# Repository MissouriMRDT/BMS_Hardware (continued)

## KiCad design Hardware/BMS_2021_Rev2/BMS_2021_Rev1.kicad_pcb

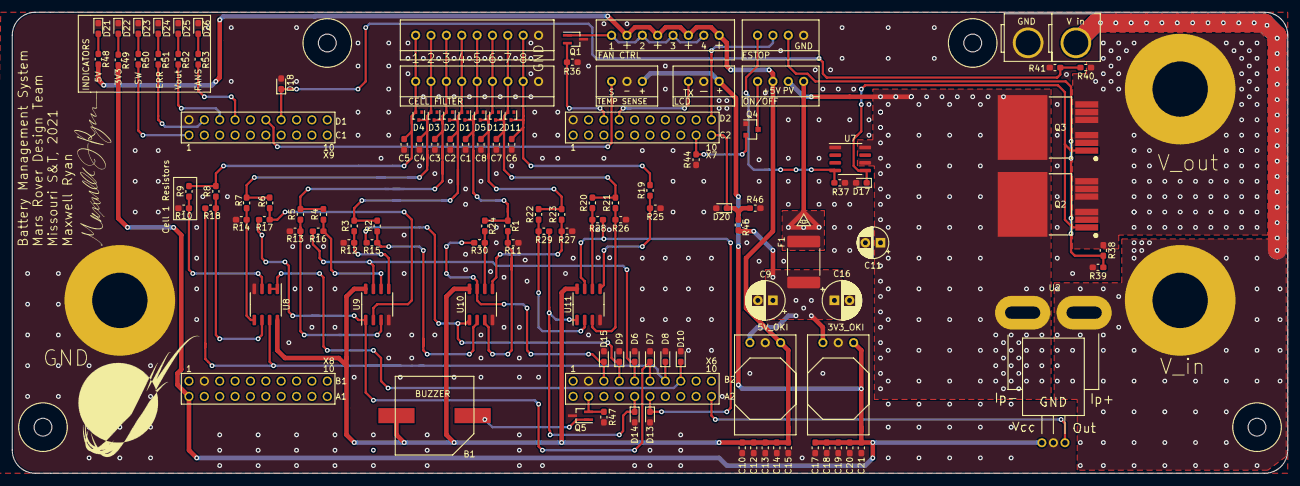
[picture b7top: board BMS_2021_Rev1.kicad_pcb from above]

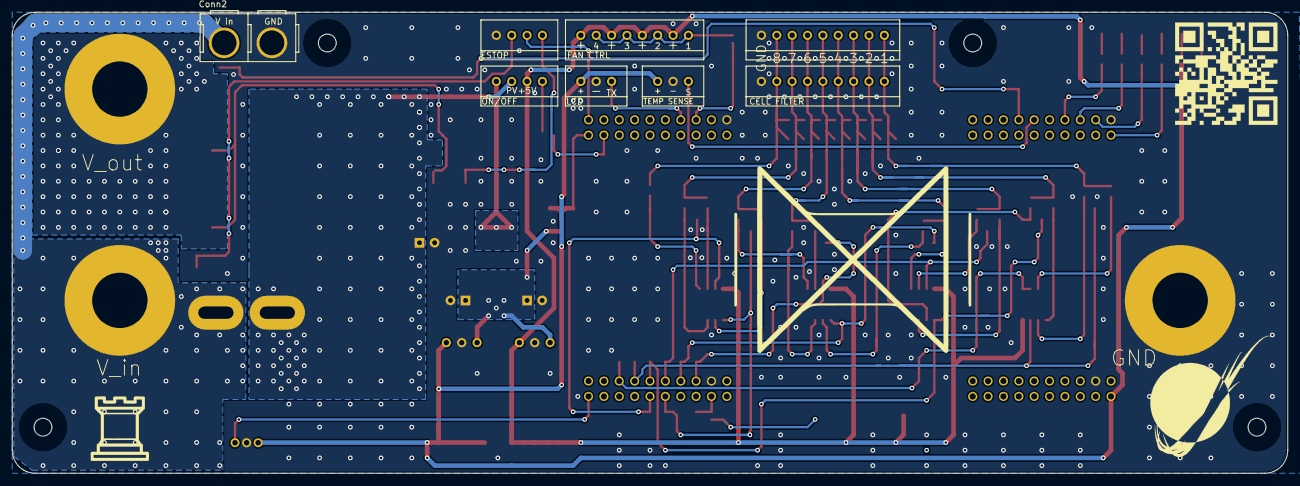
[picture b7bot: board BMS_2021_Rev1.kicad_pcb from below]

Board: 2 copper layers, 210.8 x 76.2 mm, 118 parts (8 on the bottom side), 64 nets.

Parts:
B1: Buzzer; BUZZER_SMI_1324_TW_5V_2_R
C1, C2, C3, C4, C5, C6, C7, C8: 1u; C_0603_1608Metric_Pad1.05x0.95mm_HandSolder
C9, C16: 22u 50V; CP_Radial_D6.3mm_P2.50mm
C10, C12, C13, C14, C17, C18, C19, C20: 10u; C_0603_1608Metric_Pad1.05x0.95mm_HandSolder
C11: 10u; CP_Radial_D5.0mm_P2.50mm
C15, C21: 0.1u; C_0603_1608Metric_Pad1.05x0.95mm_HandSolder
Conn1, Conn6: cell_filter; MOLEX_SL_09_Vertical
Conn2: V_in; Anderson_2_Vertical_Sidy_by_Side
Conn3, Conn7: Molex_SL_03; MOLEX_SL_03_Vertical
Conn4: Molex_SL_08; MOLEX_SL_08_Vertical
Conn5: Molex_SL_04; MOLEX_SL_04_Vertical
D1, D2, D3, D4, D5, D11, D12: 5V_Schottky; SOT-416
D6, D7, D8, D9, D10, D13, D14, D15, D17, D18, D20: 3V3_Zener; D_0603_1608Metric_Pad1.05x0.95mm_HandSolder
D21, D22, D23, D24, D25, D26: LED; LED_0603_1608Metric_Pad1.05x0.95mm_HandSolder
F1: Polyfuse; Fuse_2920_7451Metric
Q1, Q5: 2N7002PW; SOT-323_SC-70_Handsoldering
Q2, Q3: IRFS7530TRL7PP; TO127P1524X483-7N
Q4: 2N7002; SOT-23
R1, R2, R3, R4, R5, R6, R7, R8, R19, R20, R21, R22, R23, R24: 8.2M; R_0603_1608Metric_Pad1.05x0.95mm_HandSolder
R9, R36, R37, R39, R44, R47: 10k; R_0603_1608Metric_Pad1.05x0.95mm_HandSolder
R10: 36.5k; R_0603_1608Metric_Pad1.05x0.95mm_HandSolder
R11, R12, R13, R14, R15, R16, R17, R18, R25, R26, R27, R28, R29, R30: 6.34M; R_0603_1608Metric_Pad1.05x0.95mm_HandSolder
R38: 4k; R_0603_1608Metric_Pad1.05x0.95mm_HandSolder
R40, R45: 3.32M; R_0603_1608Metric_Pad1.05x0.95mm_HandSolder
R41, R46: 360k; R_0603_1608Metric_Pad1.05x0.95mm_HandSolder
R48: 500; R_0603_1608Metric_Pad1.05x0.95mm_HandSolder
R49, R50, R51, R52, R53: 330; R_0603_1608Metric_Pad1.05x0.95mm_HandSolder
SW1: Relay_SPST; MOLEX_SL_04_Vertical
U1: TM4C129E_Launchpad; TM4C129E_Launchpad_FULL_THT_TOP
U2: ACS759ECB-200B-PFF-T; ACS759ECB_PFF_Leadform_5pins
U5: 5V_OKI; OKI_Horizontal
U6: 3V3_OKI; OKI_Horizontal
U7: LT1910; LT1910_SOIC-8-1EP_3.9x4.9mm_P1.27mm_EP2.41x3.3mm
U8, U9, U10, U11: LM358; SO-8_3.9x4.9mm_P1.27mm
V1, V2, V3: BATT_PWR_VIA

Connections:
+3V3: C17.1, C18.1, C19.1, C20.1, C21.1, Conn3.3, Conn7.3, R49.1, U1.+3V3, U2.1, U6.3
+5V: B1.1, C10.1, C12.1, C13.1, C14.1, C15.1, Conn4.2, Conn4.4, Conn4.6, Conn4.8, R48.1, SW1.2, U5.3, U8.8, U9.8, U10.8, U11.8
/ESTOP/V_out: Q2.2, Q2.3, Q2.5, Q2.6, Q2.7, Q3.2, Q3.3, Q3.5, Q3.6, Q3.7, R38.1, R40.1, V3.1
/FANS_IND: R53.1, U1.PH3
/LCD_TX: Conn7.1, U1.PA7
/PV: C11.1, Q2.4, Q3.4, SW1.3, U2.5, U7.6, U7.8
/V_in: Conn2.2, U2.4, V1.1
/V_out_ind: R52.1, U1.PH2
/V_out_sense: D18.1, R40.2, R41.1, U1.PD0
/buzzer_control: Q5.2, R47.1, U1.PD2
/cell_1: C5.2, Conn1.1, Conn6.1, D4.2, R8.2, R9.2
/cell_1_sense: D10.1, U1.PK3, U8.1, U8.2
/cell_2: C4.2, Conn1.2, Conn6.2, D3.2, D4.3, R6.2, R7.2
/cell_2_sense: D8.1, R18.1, U1.PK2, U8.7
/cell_3: C3.2, Conn1.3, Conn6.3, D2.2, D3.3, R4.2, R5.2
/cell_3_sense: D7.1, R17.1, U1.PK1, U9.1
/cell_4: C2.2, Conn1.4, Conn6.4, D1.2, D2.3, R2.2, R3.2
/cell_4_sense: D6.1, R16.1, U1.PK0, U9.7
/cell_5_sense: D9.1, R15.1, U1.PB5, U10.1
/cell_6: C8.2, Conn1.6, Conn6.6, D5.3, D12.2, R22.2, R23.2
/cell_6_sense: D15.1, R30.1, U1.PB4, U10.7
/cell_7: C7.2, Conn1.7, Conn6.7, D11.2, D12.3, R20.2, R21.2
/cell_7_sense: D14.1, R29.1, U1.PD4, U11.1
/cell_8: C6.2, Conn1.8, Conn6.8, D11.3, R19.2
/cell_8_sense: D13.1, R28.1, U1.PD5, U11.7
/fan_control: Q1.2, R36.1, U1.PP5
/logic_power: C9.1, C16.1, F1.1, R45.1, U5.1, U6.1
/logic_power_sense: D20.1, R45.2, R46.1, U1.PK7
/logic_switch: Q4.2, R44.2, U1.PK6
/pack_gate: Conn5.2, U1.PM6
/pack_i_sense: U1.PN4, U2.3
/sw_err: R51.1, U1.PM3
/sw_ind: R50.1, U1.PF1
/temp_sense(A): Conn3.1, U1.PD1
E_STOP_GATE: D17.1, Q2.1, Q3.1, U7.5
GND: C1.1, C2.1, C3.1, C4.1, C5.1, C6.1, C7.1, C8.1, C9.2, C10.2, C11.2, C12.2, C13.2, C14.2, C15.2, C16.2, C17.2, C18.2, C19.2, C20.2, C21.2, Conn1.9, Conn2.1, Conn3.2, Conn5.4, Conn6.9, Conn7.2, D6.2, D7.2, D8.2, D9.2, D10.2, D13.2, D14.2, D15.2, D17.2, D18.2, D20.2, D21.1, D22.1, D23.1, D24.1, D25.1, D26.1, Q1.3, Q4.1, Q5.3, R10.2, R11.1, R12.1, R13.1, R14.1, R25.1, R26.1, R27.1, R36.2, R37.2, R39.2, R41.2, R44.1, R46.2, R47.2, U1.GND, U2.2, U5.2, U6.2, U7.1, U8.4, U9.4, U10.4, U11.4, V2.1
unnamed: B1.2, Q5.1
unnamed: Conn4.1, Conn4.3, Conn4.5, Conn4.7, Q1.1
unnamed: Conn5.1, R37.1, U7.4
unnamed: Conn5.3, R38.2, R39.1
unnamed: D21.2, R48.2
unnamed: D22.2, R49.2
unnamed: D23.2, R50.2
unnamed: D24.2, R51.2
unnamed: D25.2, R52.2
unnamed: D26.2, R53.2
unnamed: F1.2, SW1.4
unnamed: Q4.3, SW1.1
unnamed: R1.1, R11.2, U10.3
unnamed: R9.1, R10.1, U8.3
unnamed: R3.1, R12.2, U9.5
unnamed: R5.1, R13.2, U9.3
unnamed: R7.1, R14.2, U8.5
unnamed: R2.1, R15.2, U10.2
unnamed: R4.1, R16.2, U9.6
unnamed: R6.1, R17.2, U9.2
unnamed: R8.1, R18.2, U8.6
unnamed: R19.1, R25.2, U11.5
unnamed: R20.1, R28.2, U11.6
unnamed: R21.1, R26.2, U11.3
unnamed: R22.1, R29.2, U11.2
unnamed: R23.1, R27.2, U10.5
unnamed: R24.1, R30.2, U10.6
cell_5_extension: C1.2, Conn1.5, Conn6.5, D1.3, D5.2, R1.2, R24.2

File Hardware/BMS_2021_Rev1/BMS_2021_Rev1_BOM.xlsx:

Reference | Quantity | Value | Footprint | Datasheet | MANUFACTURER
B1 | 1 | Buzzer | MRDT_Devices:BUZZER_SMI_1324_TW_5V_2_R
C1 C2 C3 C4 C5 C8 C7 C6 | 8 | 1u | Capacitor_SMD:C_0603_1608Metric_Pad1.05x0.95mm_HandSolder | ~
C10 C12 C13 C14 C17 C18 C19 C20 | 8 | 10u | Capacitor_SMD:C_0603_1608Metric_Pad1.05x0.95mm_HandSolder | ~
C11 | 1 | 10u | Capacitor_THT:CP_Radial_D5.0mm_P2.50mm | https://www.digikey.com/en/products/detail/nichicon/UVR1H100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
C15 C21 | 2 | 0.1u | Capacitor_SMD:C_0603_1608Metric_Pad1.05x0.95mm_HandSolder | ~
C9 C16 | 2 | 22u 50V | Capacitor_THT:CP_Radial_D6.3mm_P2.50mm | ~
Conn1 Conn6 | 2 | cell_filter | MRDT_Connectors:MOLEX_SL_09_Vertical
Conn2 | 1 | V_in | MRDT_Connectors:Anderson_2_Vertical_Sidy_by_Side
Conn3 Conn7 | 2 | Molex_SL_03 | MRDT_Connectors:MOLEX_SL_03_Vertical
Conn4 | 1 | Molex_SL_08 | MRDT_Connectors:MOLEX_SL_08_Vertical
Conn5 | 1 | Molex_SL_04 | MRDT_Connectors:MOLEX_SL_04_Vertical
D10 D8 D7 D6 D9 D15 D14 D13 D18 D17 D20 | 11 | 3V3_Zener | Diode_SMD:D_0603_1608Metric_Pad1.05x0.95mm_HandSolder | ~
D21 D26 D25 D24 D23 D22 | 6 | LED | LED_SMD:LED_0603_1608Metric_Pad1.05x0.95mm_HandSolder | ~
D4 D3 D2 D5 D12 D1 D11 | 7 | 5V_Schottky | MRDT_BMS2021:RB886CST2RA | https://www.digikey.com/en/products/detail/rohm-semiconducto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
F1 | 1 | Polyfuse | Fuse:Fuse_2920_7451Metric | ~
Q1 Q5 | 2 | 2N7002PW | Package_TO_SOT_SMD:SOT-323_SC-70_Handsoldering | https://www.digikey.com/en/products/detail/nexperia-usa-inc/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
Q2 Q3 | 2 | IRFS7530TRL7PP | MRDT_BMS2021:TO127P1524X483-7N | https://www.digikey.com/en/products/detail/infineon-technolo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 | International Rectifier
Q4 | 1 | 2N7002 | Package_TO_SOT_SMD:SOT-23 | https://www.digikey.com/en/products/detail/on-semiconductor/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
R10 | 1 | 36.5k | Resistor_SMD:R_0603_1608Metric_Pad1.05x0.95mm_HandSolder | ~
R18 R14 R17 R13 R16 R12 R15 R11 R30 R27 R29 R26 R28 R25 | 14 | 6.34M | Resistor_SMD:R_0603_1608Metric_Pad1.05x0.95mm_HandSolder | ~
R36 R47 | 2 | 10kÎ© | Resistor_SMD:R_0603_1608Metric_Pad1.05x0.95mm_HandSolder | ~
R38 | 1 | 4k | Resistor_SMD:R_0603_1608Metric_Pad1.05x0.95mm_HandSolder | ~
R40 R45 | 2 | 1.01M | Resistor_SMD:R_0603_1608Metric_Pad1.05x0.95mm_HandSolder | ~
R41 R46 | 2 | 110k | Resistor_SMD:R_0603_1608Metric_Pad1.05x0.95mm_HandSolder | ~
R48 | 1 | 500 | Resistor_SMD:R_0603_1608Metric_Pad1.05x0.95mm_HandSolder | ~
R53 R52 R49 R50 R51 | 5 | 330 | Resistor_SMD:R_0603_1608Metric_Pad1.05x0.95mm_HandSolder | ~
R8 R7 R6 R5 R4 R3 R1 R24 R23 R22 R21 R20 R19 R2 | 14 | 8.2M | Resistor_SMD:R_0603_1608Metric_Pad1.05x0.95mm_HandSolder | ~
R9 R37 R39 R44 | 4 | 10k | Resistor_SMD:R_0603_1608Metric_Pad1.05x0.95mm_HandSolder | ~
SW1 | 1 | Relay_SPST | MRDT_Connectors:MOLEX_SL_04_Vertical
U1 | 1 | TM4C129E_Launchpad | MRDT_Shields:TM4C129E_Launchpad_FULL_SMD_TOP
U2 | 1 | ACS759ECB-200B-PFF-T | MRDT_Sensors:ACS759ECB_PFF_Leadform_5pins
U3 U4 | 2 | TL3474ACPWR | MRDT_BMS2021:TL3474ID
U5 | 1 | 5V_OKI | MRDT_Devices:OKI_Horizontal | https://www.digikey.com/product-detail/en/murata-power-solut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
U6 | 1 | 3V3_OKI | MRDT_Devices:OKI_Horizontal | https://www.digikey.com/product-detail/en/murata-power-solut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
U7 | 1 | LT1910 | MRDT_BMS2021:LT1910_SOIC-8-1EP_3.9x4.9mm_P1.27mm_EP2.41x3.3mm
V1 V2 V3 | 3 | BATT_PWR_VIA | MRDT_Drill_Holes:BATT_PWR_VIA

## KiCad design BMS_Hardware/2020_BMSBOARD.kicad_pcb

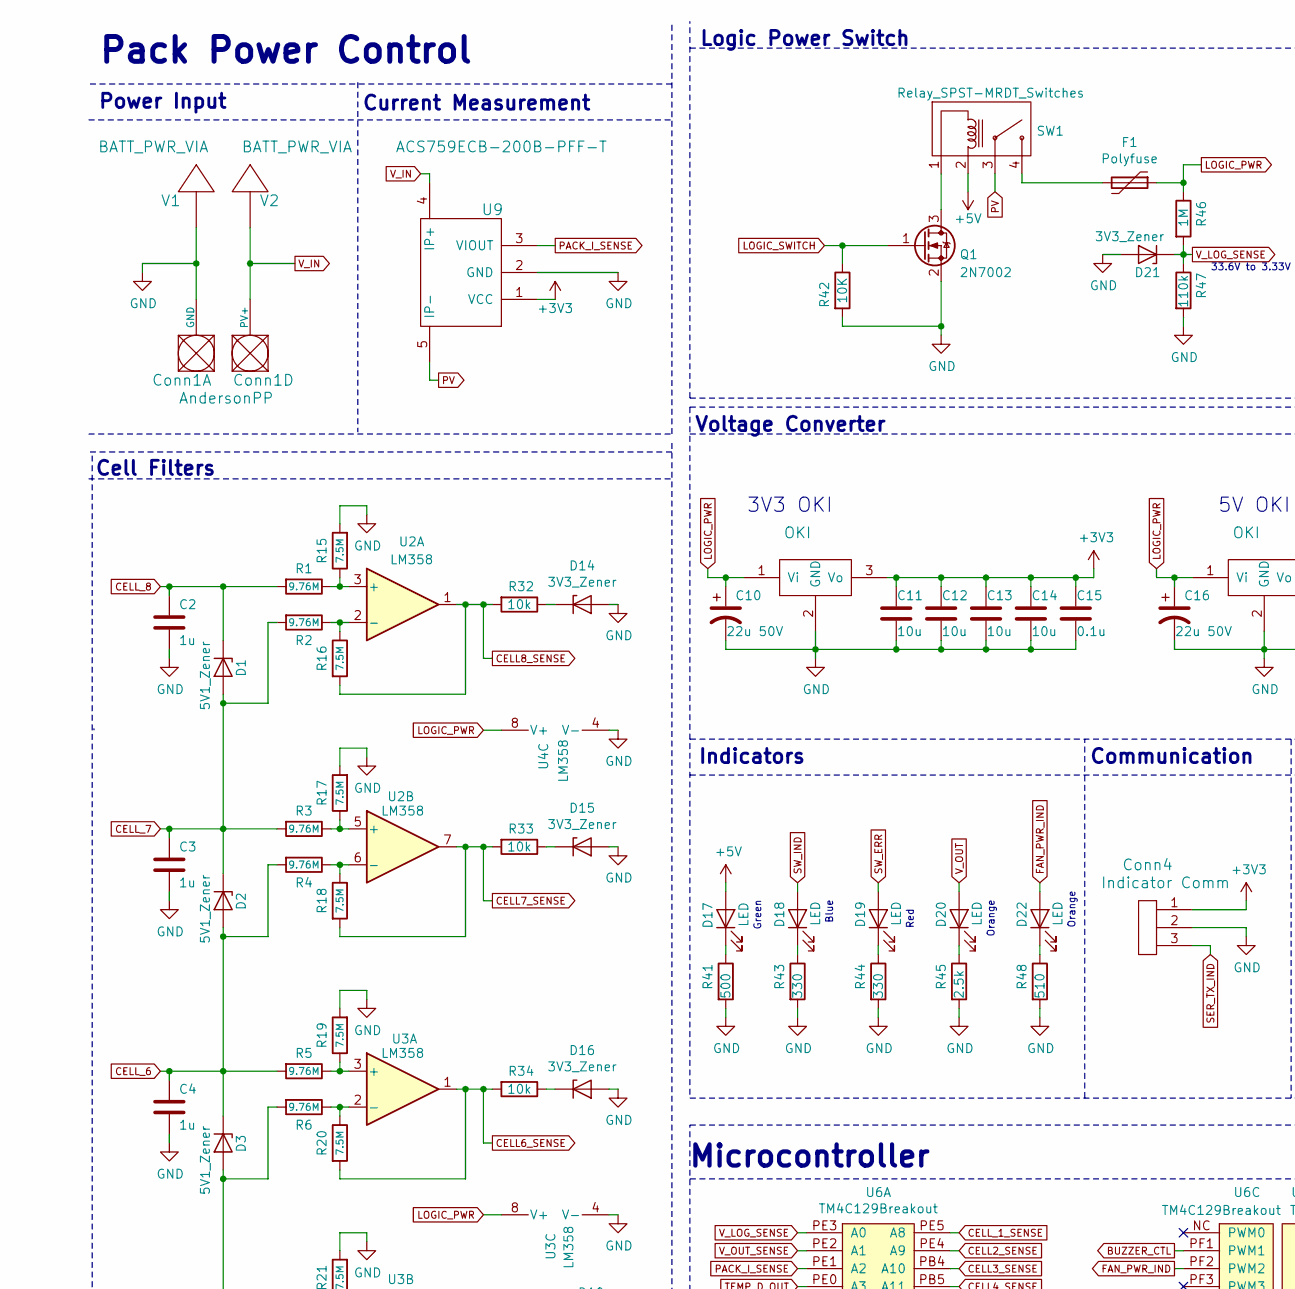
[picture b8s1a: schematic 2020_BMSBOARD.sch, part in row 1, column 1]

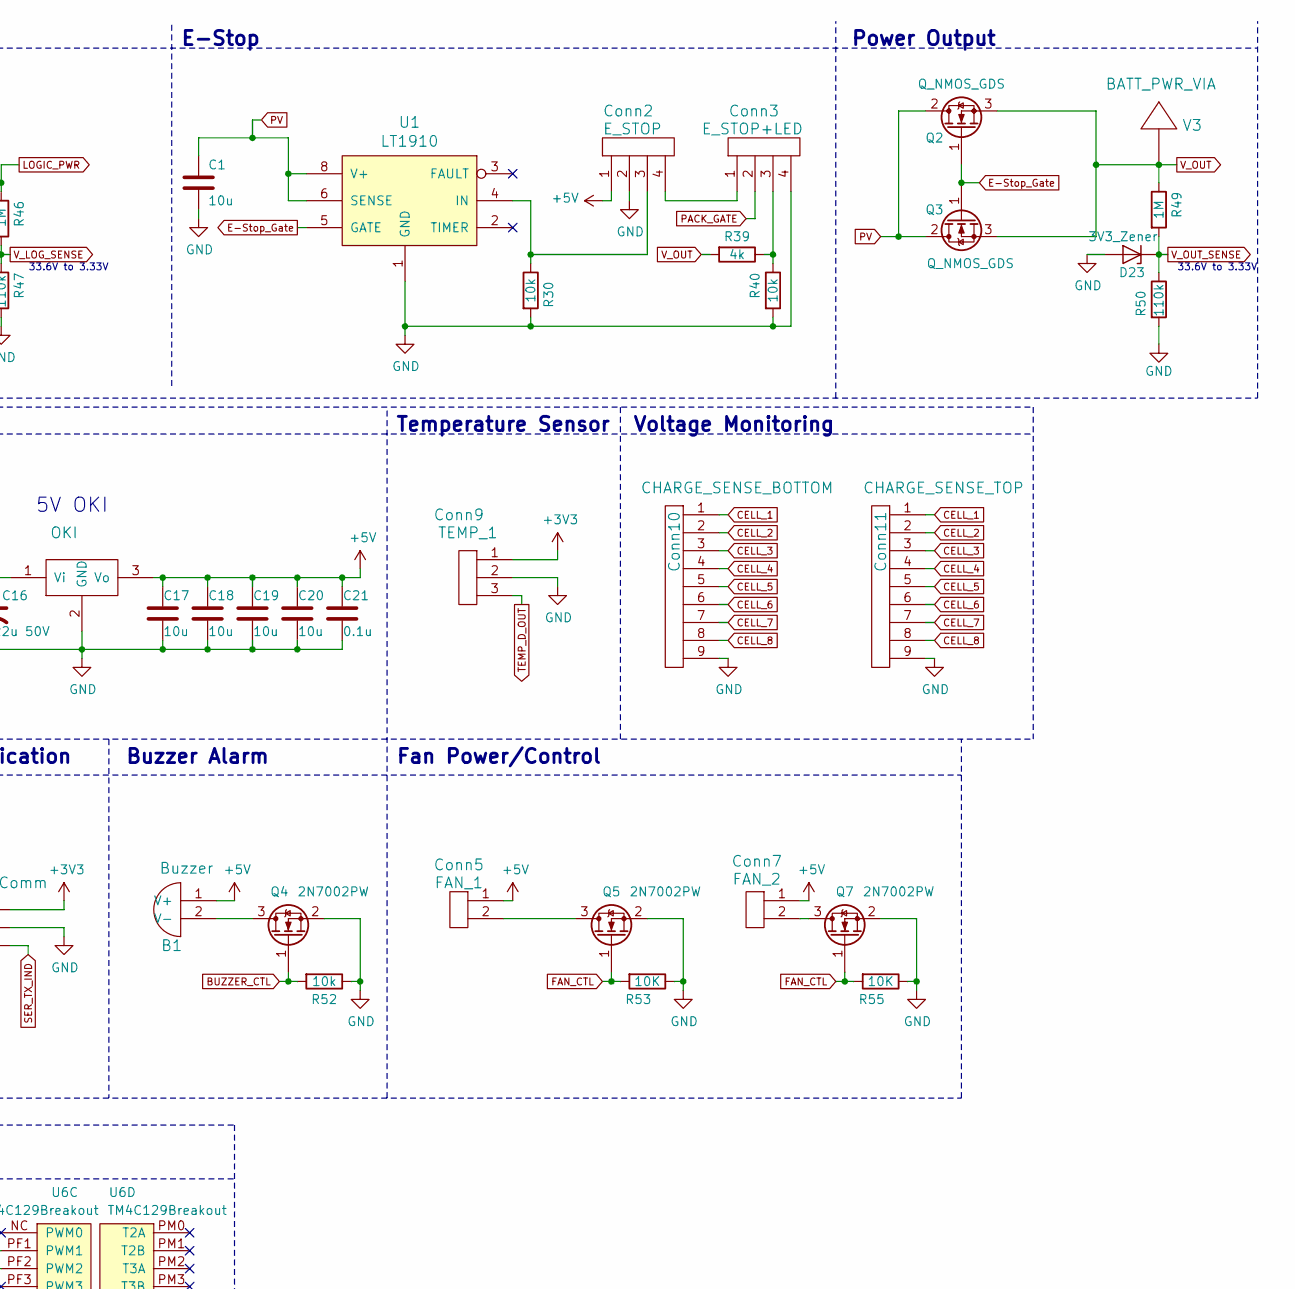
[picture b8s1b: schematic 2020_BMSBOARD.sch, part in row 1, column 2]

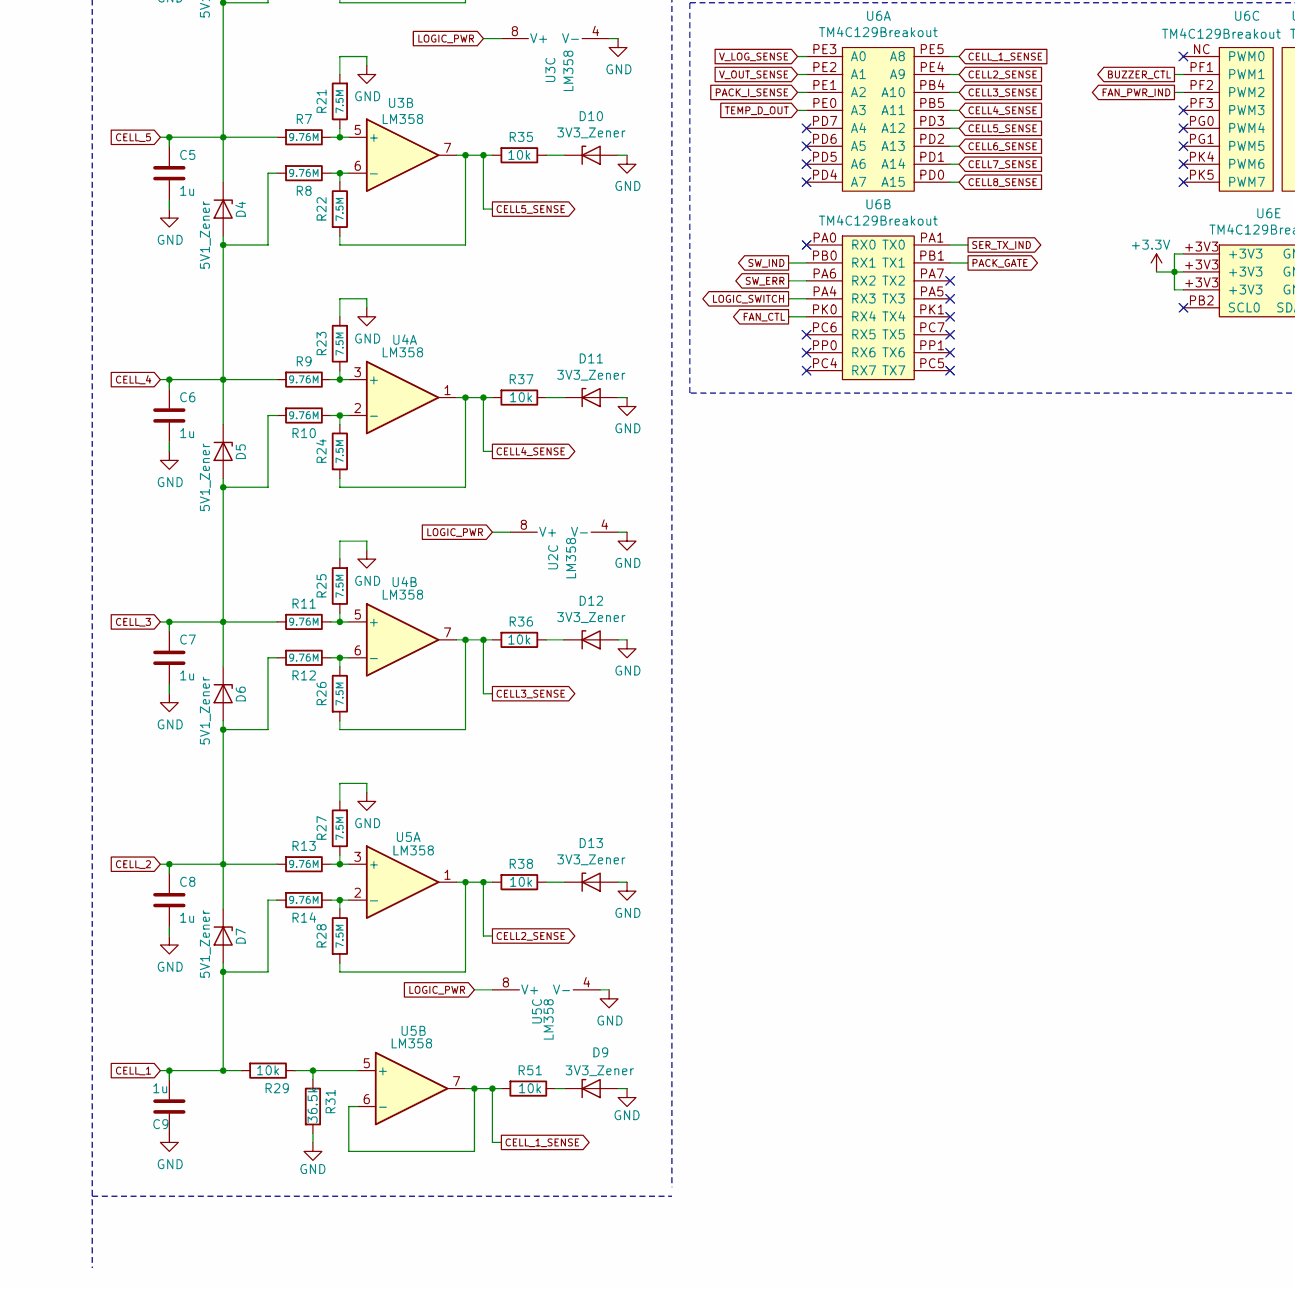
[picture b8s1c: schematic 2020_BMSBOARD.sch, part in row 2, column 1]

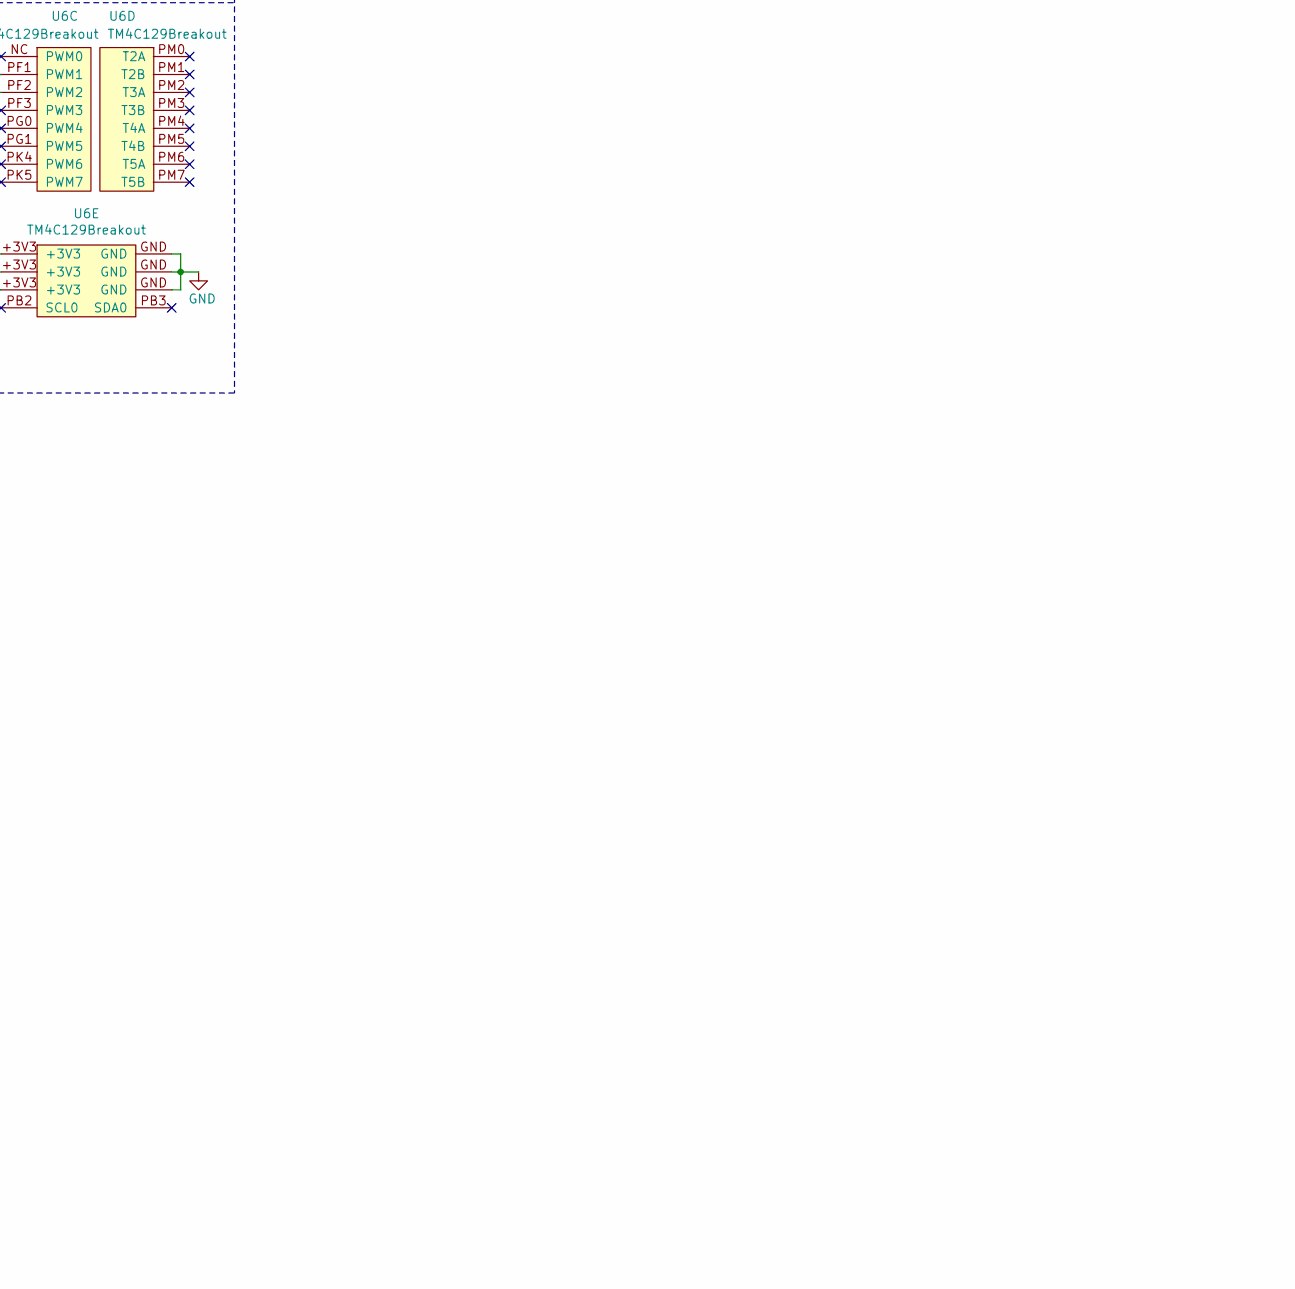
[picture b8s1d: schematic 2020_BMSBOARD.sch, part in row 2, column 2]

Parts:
B1: Buzzer; BUZZER_SMI_1324_TW_5V_2_R
C1: 10u; C_1206_3216Metric_Pad1.42x1.75mm_HandSolder
C2, C3, C4, C5, C6, C7, C8, C9: 1u; C_0603_1608Metric_Pad1.05x0.95mm_HandSolder
C10, C16: 22u 50V; CP_Radial_D6.3mm_P2.50mm
C11, C12, C13, C14, C17, C18, C19, C20: 10u; C_0603_1608Metric_Pad1.05x0.95mm_HandSolder
C15, C21: 0.1u; C_0603_1608Metric_Pad1.05x0.95mm_HandSolder
Conn1: AndersonPP; Anderson_2_Vertical_Sidy_by_Side
Conn2: E_STOP; MOLEX_SL_04_Vertical
Conn3: E_STOP+LED; MOLEX_SL_04_Vertical
Conn4: Indicator Comm; MOLEX_SL_03_Vertical
Conn5: FAN_1; MOLEX_SL_02_Vertical
Conn7: FAN_2; MOLEX_SL_02_Vertical
Conn9: TEMP_1; MOLEX_SL_03_Vertical
Conn10: CHARGE_SENSE_BOTTOM; MOLEX_SL_09_Vertical
Conn11: CHARGE_SENSE_TOP; MOLEX_SL_09_Vertical
D1, D2, D3, D4, D5, D6, D7: 5V1_Zener; D_SOD-323_HandSoldering
D9, D10, D11, D12, D13, D14, D15, D16, D21, D23: 3V3_Zener; D_SOD-323_HandSoldering
D17, D18, D19, D20, D22: LED; LED_0603_1608Metric_Pad1.05x0.95mm_HandSolder
F1: Polyfuse; Fuse_2920_7451Metric
Q1: 2N7002; SOT-23
Q2, Q3: Q_NMOS_GDS; IRLS3034_TO-263-7_P
Q4, Q5, Q7: 2N7002PW; SOT-23
R1, R2, R3, R4, R5, R6, R7, R8, R9, R10, R11, R12, R13, R14: 9.76M; R_0603_1608Metric_Pad1.05x0.95mm_HandSolder
R15, R16, R17, R18, R19, R20, R21, R22, R23, R24, R25, R26, R27, R28: 7.5M; R_0603_1608Metric_Pad1.05x0.95mm_HandSolder
R29, R30, R32, R33, R34, R35, R36, R37, R38, R40, R51, R52: 10k; R_0603_1608Metric_Pad1.05x0.95mm_HandSolder
R31: 36.5k; R_0603_1608Metric_Pad1.05x0.95mm_HandSolder
R39: 4k; R_0603_1608Metric_Pad1.05x0.95mm_HandSolder
R41: 500; R_0603_1608Metric_Pad1.05x0.95mm_HandSolder
R42, R53, R55: 10K; R_0603_1608Metric_Pad1.05x0.95mm_HandSolder
R43, R44: 330; R_0603_1608Metric_Pad1.05x0.95mm_HandSolder
R45: 2.5k; R_0603_1608Metric_Pad1.05x0.95mm_HandSolder
R46, R49: 1M; R_0603_1608Metric_Pad1.05x0.95mm_HandSolder
R47, R50: 110k; R_0603_1608Metric_Pad1.05x0.95mm_HandSolder
R48: 510; R_0603_1608Metric_Pad1.05x0.95mm_HandSolder
SW1: Relay_SPST-MRDT_Switches; MOLEX_SL_04_Vertical
U1: LT1910; LT1910_SOIC-8-1EP_3.9x4.9mm_P1.27mm_EP2.41x3.3mm
U2, U3, U4, U5: LM358; SOIC-8_3.9x4.9mm_P1.27mm
U6: TM4C129Breakout; TM4C129Breakout_THT
U9: ACS759ECB-200B-PFF-T; ACS759ECB_PFF_Leadform_5pins
U10, U12: OKI; OKI_Horizontal
V1, V2, V3: BATT_PWR_VIA

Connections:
+5V: B1.1 (V+), C17.1, C18.1, C19.1, C20.1, C21.1, Conn2.1, Conn5.1, Conn7.1, D17.2 (A), SW1.2, U12.3 (Vo)
BUZZER_CTL: Q4.1 (G), R52.2, U6.PF1 (PWM1)
CELL2_SENSE: R28.2, R38.2, U5.1, U6.PE4 (A9)
CELL3_SENSE: R26.2, R36.2, U4.7, U6.PB4 (A10)
CELL4_SENSE: R24.2, R37.2, U4.1, U6.PB5 (A11)
CELL5_SENSE: R22.2, R35.2, U3.7, U6.PD3 (A12)
CELL6_SENSE: R20.2, R34.2, U3.1, U6.PD2 (A13)
CELL7_SENSE: R18.2, R33.2, U2.7, U6.PD1 (A14)
CELL8_SENSE: R16.2, R32.2, U2.1, U6.PD0 (A15)
CELL_1: C9.1, Conn10.1, Conn11.1, D7.2 (A), R14.2, R29.2
CELL_1_SENSE: R51.2, U5.6 (-), U5.7, U6.PE5 (A8)
CELL_2: C8.1, Conn10.2, Conn11.2, D6.2 (A), D7.1 (K), R12.2, R13.2
CELL_3: C7.1, Conn10.3, Conn11.3, D5.2 (A), D6.1 (K), R10.2, R11.2
CELL_4: C6.1, Conn10.4, Conn11.4, D4.2 (A), D5.1 (K), R8.2, R9.2
CELL_5: C5.1, Conn10.5, Conn11.5, D3.2 (A), D4.1 (K), R6.2, R7.2
CELL_6: C4.1, Conn10.6, Conn11.6, D2.2 (A), D3.1 (K), R4.2, R5.2
CELL_7: C3.1, Conn10.7, Conn11.7, D1.2 (A), D2.1 (K), R2.2, R3.2
CELL_8: C2.1, Conn10.8, Conn11.8, D1.1 (K), R1.2
E-Stop_Gate: Q2.1 (G), Q3.1 (G), U1.5 (GATE)
FAN_CTL: Q5.1 (G), Q7.1 (G), R53.2, R55.2, U6.PK0 (RX4)
FAN_PWR_IND: D22.2 (A), U6.PF2 (PWM2)
GND: C1.2, C2.2, C3.2, C4.2, C5.2, C6.2, C7.2, C8.2, C9.2, C10.2, C11.2, C12.2, C13.2, C14.2, C15.2, C16.2, C17.2, C18.2, C19.2, C20.2, C21.2, Conn1.1 (GND), Conn2.2, Conn3.4, Conn4.2, Conn9.2, Conn10.9, Conn11.9, D9.2 (A), D10.2 (A), D11.2 (A), D12.2 (A), D13.2 (A), D14.2 (A), D15.2 (A), D16.2 (A), D21.2 (A), D23.2 (A), Q1.2 (S), Q4.2 (S), Q5.2 (S), Q7.2 (S), R15.2, R17.2, R19.2, R21.2, R23.2, R25.2, R27.2, R30.2, R31.2, R40.2, R41.2, R42.2, R43.2, R44.2, R45.2, R47.2, R48.2, R50.2, R52.1, R53.1, R55.1, U1.1 (GND), U2.4 (V-), U3.4 (V-), U4.4 (V-), U5.4 (V-), U6.GND, U9.2 (GND), U10.2 (GND), U12.2 (GND), V1.1
LOGIC_PWR: C10.1, C16.1, F1.1, R46.1, U2.8 (V+), U3.8 (V+), U4.8 (V+), U5.8 (V+), U10.1 (Vi), U12.1 (Vi)
LOGIC_SWITCH: Q1.1 (G), R42.1, U6.PA4 (RX3)
unnamed: B1.2 (V-), Q4.3 (D)
unnamed: Conn2.3, R30.1, U1.4 (IN)
unnamed: Conn2.4, Conn3.1
unnamed: Conn3.3, R39.1, R40.1
unnamed: Conn5.2, Q5.3 (D)
unnamed: Conn7.2, Q7.3 (D)
unnamed: D9.1 (K), R51.1
unnamed: D10.1 (K), R35.1
unnamed: D11.1 (K), R37.1
unnamed: D12.1 (K), R36.1
unnamed: D13.1 (K), R38.1
unnamed: D14.1 (K), R32.1
unnamed: D15.1 (K), R33.1
unnamed: D16.1 (K), R34.1
unnamed: D17.1 (K), R41.1
unnamed: D18.1 (K), R43.1
unnamed: D19.1 (K), R44.1
unnamed: D20.1 (K), R45.1
unnamed: D22.1 (K), R48.1
unnamed: F1.2, SW1.4
unnamed: Q1.3 (D), SW1.1
unnamed: R1.1, R15.1, U2.3 (+)
unnamed: R10.1, R24.1, U4.2 (-)
unnamed: R11.1, R25.1, U4.5 (+)
unnamed: R12.1, R26.1, U4.6 (-)
unnamed: R13.1, R27.1, U5.3 (+)
unnamed: R14.1, R28.1, U5.2 (-)
unnamed: R2.1, R16.1, U2.2 (-)
unnamed: R3.1, R17.1, U2.5 (+)
unnamed: R4.1, R18.1, U2.6 (-)
unnamed: R5.1, R19.1, U3.3 (+)
unnamed: R6.1, R20.1, U3.2 (-)
unnamed: R7.1, R21.1, U3.5 (+)
unnamed: R8.1, R22.1, U3.6 (-)
unnamed: R9.1, R23.1, U4.3 (+)
unnamed: R29.1, R31.1, U5.5 (+)
PACK_GATE: Conn3.2, U6.PB1 (TX1)
PACK_I_SENSE: U6.PE1 (A2), U9.3 (VIOUT)
PV: C1.1, Q2.2 (D), Q3.2 (D), SW1.3, U1.6 (SENSE), U1.8 (V+), U9.5 (IP-)
SER_TX_IND: Conn4.3, U6.PA1 (TX0)
SW_ERR: D19.2 (A), U6.PA6 (RX2)
SW_IND: D18.2 (A), U6.PB0 (RX1)
TEMP_D_OUT: Conn9.3, U6.PE0 (A3)
V_IN: Conn1.2 (V+Log), Conn1.4 (PV+), U9.4 (IP+), V2.1
V_LOG_SENSE: D21.1 (K), R46.2, R47.1, U6.PE3 (A0)
V_OUT: D20.2 (A), Q2.3 (S), Q3.3 (S), R39.2, R49.1, V3.1
V_OUT_SENSE: D23.1 (K), R49.2, R50.1, U6.PE2 (A1)

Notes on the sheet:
Power Input
Current Measurement
E-Stop
Pack Power Control
Logic Power Switch
3V3 OKI
5V OKI
Voltage Converter
Orange
Red
Blue
Indicators
Communication
Buzzer Alarm
Voltage Monitoring
Fan Power/Control
Cell Filters
Microcontroller
Green
Temperature Sensor
Power Output
33.6V to 3.33V

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
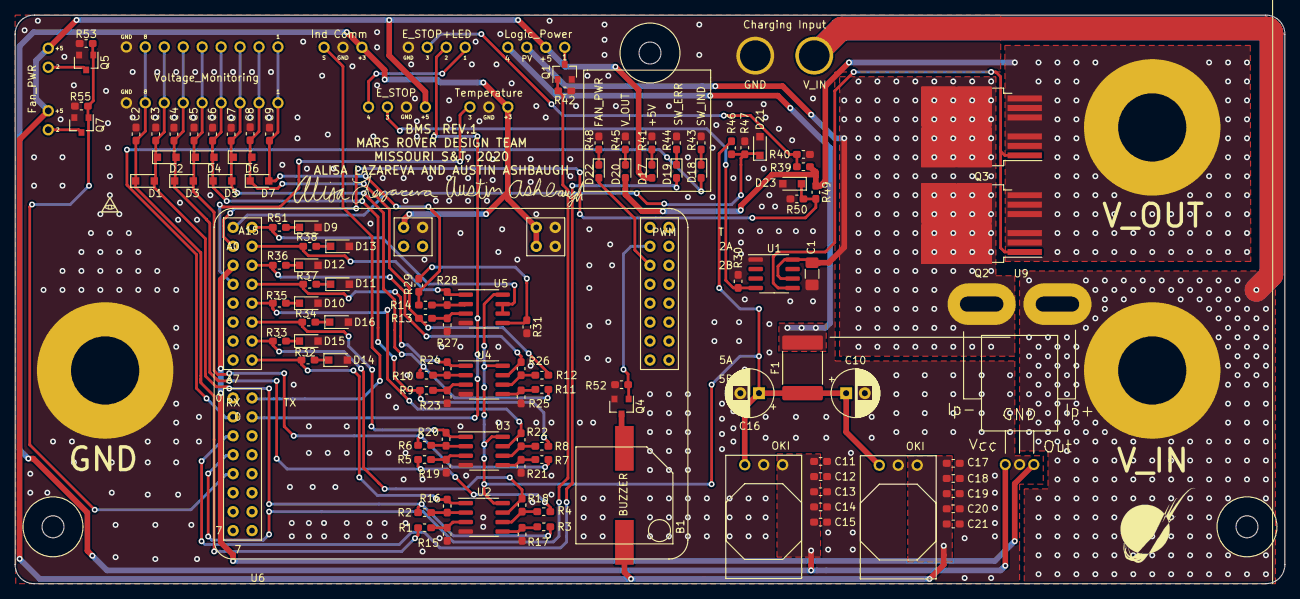
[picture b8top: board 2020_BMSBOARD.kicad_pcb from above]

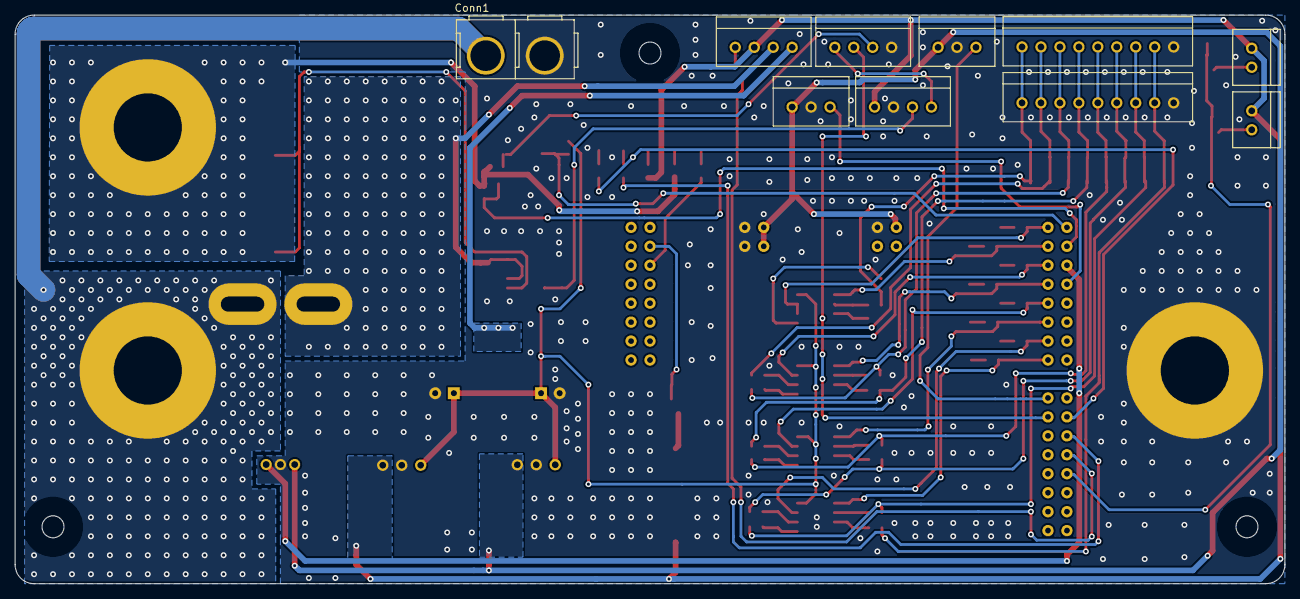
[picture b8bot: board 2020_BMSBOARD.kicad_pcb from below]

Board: 2 copper layers, 170.2 x 76.2 mm, 127 parts (10 on the bottom side), 72 nets.

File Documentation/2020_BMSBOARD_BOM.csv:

Id,Designator,Package,Quantity,Designation,Item Name,Part Number,Vendor, Cost per Item , Cost ,URL,Comments
1,Conn4,MOLEX_SL_03_Vertical,1,Indicator Comm,CONN HEADER 3POS .100 VERT GOLD,WM4801-ND,Digikey, $0.92 , $0.92 ,https://www.digikey.com/products/en?keywords=WM4801-ND,
2,Conn9,MOLEX_SL_03_Vertical,1,TEMP_1,CONN HEADER 3POS .100 VERT GOLD,WM4801-ND,Digikey, $0.92 , $0.92 ,https://www.digikey.com/products/en?keywords=WM4801-ND,
3,B1,BUZZER_SMI_1324_TW_5V_2_R,1,Buzzer,AUDIO MAGNETIC IND 4-7V SMD,"	668-1336-1-ND",Digikey, $6.12 , $6.12 ,https://www.Digikey.com/product-detail/en/pui-audio-inc/SMI-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,
4,Conn2,MOLEX_SL_04_Vertical,1,E_STOP,"CONN HEADER 4POS .100 VERT GOLD	",WM4802-ND,Digikey, $0.44 , $0.44 ,https://www.digikey.com/product-detail/en/molex-llc/07054300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,
5,"D13,D9,D16,D14,D10,D11,D12,D15,D23",D_SOD-323_HandSoldering,9,3V3,Zener Diode 3.3V 200mW ±2% Surface Mount SOD-323F,MM3Z3V3BCT-ND,Digikey, $0.21 , $1.89 ,https://www.digikey.com/product-detail/en/on-semiconductor/M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,
6,"U4,U2,U5,U3",SOIC-8_3.9x4.9mm_P1.27mm,4,LM358,LM358DT,497-1591-1-ND,Digikey, $0.46 , $1.84 ,https://www.digikey.com/product-detail/en/stmicroelectronics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,
7,"D7,D6,D5,D4,D3,D2,D1,D8",D_SOD-323_HandSoldering,8,5.1V,Zener Diode 5.1V 300mW ±2% Surface Mount SOD-323,MM3Z5V1ST1GOSCT-ND,Digikey, $0.13 , $1.04 ,https://www.digikey.com/product-detail/en/on-semiconductor/M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,
8,Conn7,MOLEX_SL_02_Vertical,1,FAN_2,CONN HEADER 2POS .100 VERT GOLD,"WM4800-ND	",Digikey, $0.84 , $0.84 ,https://www.digikey.com/products/en?keywords=WM4800-ND,
9,Conn10,MOLEX_SL_09_Vertical,1,CHARGE_SENSE_BOTTOM,"CONN HEADER 9POS .100 VERT GOLD	",WM4807-ND,Digikey, $2.07 , $2.07 ,https://www.Digikey.com/product-detail/en/molex-llc/07054300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,
10,"R8,R1,R2,R3,R4,R5,R6,R7,R9,R10,R11,R12,R13,R14",R_0603_1608Metric_Pad1.05x0.95mm_HandSolder,14,9.76M,"9.76 MOhms ±1% 0.1W, 1/10W Chip Resistor 0603 (1608 Metric) Automotive AEC-Q200 Thick Film",541-9.76MHCT-ND,Digikey, $0.10 , $1.40 ,https://www.digikey.com/product-detail/en/vishay-dale/CRCW06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,
11,"R33,R38,R37,R36,R35,R34,R32,R29,R30,R40,R50,R52",R_0603_1608Metric_Pad1.05x0.95mm_HandSolder,12,10k,RES SMD 10K OHM 1% 1/4W 0603,RHM10KADCT-ND,Digikey, $0.14 , $1.68 ,https://www.digikey.com/product-detail/en/rohm-semiconductor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,
12,U1,LT1910_SOIC-8-1EP_3.9x4.9mm_P1.27mm_EP2.41x3.3mm,1,LT1910,"	IC MOSFET DRIVER HI-SIDE 8-SOIC",LT1910IS8#PBF-ND,Digikey, $4.61 , $4.61 ,https://www.Digikey.com/products/en?keywords=LT1910IS8%23PBF,
14,U9,ACS759ECB_PFF_Leadform_5pins,1,ACS759ECB-200B-PFF-T,SENSOR CURRENT HALL 200A AC/DC ,620-1466-5-ND,Digikey, $8.38 , $8.38 ,https://www.Digikey.com/products/en?keywords=%20620-1466-5-ND%20,
16,"Q2,Q3",IRLS3034_TO-263-7_P,2,Q_NMOS_GDS,"IRLS3034-7PPBF	","IRLS3034-7PPBF-ND	",Digikey, $6.92 , $13.84 ,https://www.Digikey.com/products/en?keywords=irls3034-7ppbf,
17,"C2,C3,C4,C5,C6,C7,C8,C9",C_0603_1608Metric_Pad1.05x0.95mm_HandSolder,8,1u,"CAP CER 1UF 6.3V X5R 0603	",1276-1036-1-ND,Digikey, $0.10 , $0.80 ,https://www.digikey.com/product-detail/en/samsung-electro-me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,
18,"C11,C12,C13,C14,C17,C18,C19,C20",C_0603_1608Metric_Pad1.05x0.95mm_HandSolder,8,10u,CAP CER 10UF 16V X5R 0603,587-3238-1-ND,Digikey, $0.45 , $3.60 ,https://www.Digikey.com/product-detail/en/taiyo-yuden/EMK107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,
19,"C15,C21",C_0603_1608Metric_Pad1.05x0.95mm_HandSolder,2,0.1u,CAP CER 0.1UF 16V X7R 0603,"1276-1005-1-ND	",Digikey, $0.10 , $0.20 ,https://www.digikey.com/product-detail/en/samsung-electro-me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,
,Conn1,,,,Red Housing,1327,Powerwerx, $0.37 , $0.37 ,https://powerwerx.com/anderson-powerpole-colored-housings,
,Conn1,,,,Black Housing,1327G6,Powerwerx, $0.37 , $0.37 ,https://powerwerx.com/anderson-powerpole-colored-housings,
20,Conn1,Anderson_2_Vertical_Sidy_by_Side,2,AndersonPP,,,Powerwerx, $0.59 , $1.18 ,https://powerwerx.com/anderson-1335g1-printed-circuit-board-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,
21,Conn3,MOLEX_SL_04_Vertical,1,E_STOP+LED,CONN HEADER 4POS .100 VERT GOLD,WM4802-ND,Digikey, $0.44 , $0.44 ,https://www.digikey.com/product-detail/en/molex-llc/07054300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,
22,Conn5,MOLEX_SL_02_Vertical,1,FAN_1,CONN HEADER 2POS .100 VERT GOLD,"WM4800-ND	",Digikey, $0.84 , $0.84 ,https://www.digikey.com/products/en?keywords=WM4800-ND,
23,Conn11,MOLEX_SL_09_Vertical,1,CHARGE_SENSE_TOP,"CONN HEADER 9POS .100 VERT GOLD	",WM4807-ND,Digikey, $2.07 , $2.07 ,https://www.Digikey.com/product-detail/en/molex-llc/07054300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,
,D17,LED_0603_1608Metric_Pad1.05x0.95mm_HandSolder,1,5V LED,Green 0603,160-1446-1-ND,Digikey,, $-   ,https://www.digikey.com/product-detail/en/lite-on-inc/LTST-C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,
,D18,LED_0603_1608Metric_Pad1.05x0.95mm_HandSolder,1,SW_IND LED,LED BLUE CLEAR CHIP SMD,160-1647-1-ND,Digikey, $0.53 , $0.53 ,https://www.Digikey.com/product-detail/en/lite-on-inc/LTST-C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,
,"D20,D22",LED_0603_1608Metric_Pad1.05x0.95mm_HandSolder,2,"V_OUT, FAN_PWR_IND LED","LED ORANGE CLEAR SMD	",160-1445-1-ND,Digikey, $0.27 , $0.54 ,https://www.Digikey.com/product-detail/en/lite-on-inc/LTST-C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,
24,D19,LED_0603_1608Metric_Pad1.05x0.95mm_HandSolder,1,SWR_ERR LED,LED RED CLEAR SMD,160-1447-1-ND,Digikey, $0.29 , $0.29 ,https://www.Digikey.com/product-detail/en/lite-on-inc/LTST-C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,
25,D21,D_SOD-323_HandSoldering,1,3V3,,,Digikey,, $-   ,,
26,Q1,SOT-23,1,2N7002,,,Digikey,, $-   ,,
27,"Q4,Q5,Q7",SOT-23,3,2N7002PW,,,Digikey,, $-   ,,
28,"R15,R16,R17,R18,R19,R20,R21,R22,R23,R24,R25,R26,R27,R28",R_0603_1608Metric_Pad1.05x0.95mm_HandSolder,14,7.5M,"7.5 MOhms ±1% 0.1W, 1/10W Chip Resistor 0603 (1608 Metric) Automotive AEC-Q200 Thick Film",RMCF0603FT7M50CT-ND,Digikey, $0.10 , $1.40 ,https://www.digikey.com/product-detail/en/stackpole-electron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,
29,R31,R_0603_1608Metric_Pad1.05x0.95mm_HandSolder,1,36.5k,,,Digikey,, $-   ,,
30,R39,R_0603_1608Metric_Pad1.05x0.95mm_HandSolder,1,4k,RES SMD 4.02K OHM 1% 1/10W 0603,"RHM4.02KBJCT-ND	",Digikey, $0.15 , $0.15 ,https://www.digikey.com/product-detail/en/rohm-semiconductor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,
31,R41,R_0603_1608Metric_Pad1.05x0.95mm_HandSolder,1,500,,,Digikey,, $-   ,,
32,"R42,R53,R55",R_0603_1608Metric_Pad1.05x0.95mm_HandSolder,3,10K,,,Digikey,, $-   ,,
33,"R43,R44,R48",R_0603_1608Metric_Pad1.05x0.95mm_HandSolder,3,330,,,Digikey,, $-   ,,
34,R45,R_0603_1608Metric_Pad1.05x0.95mm_HandSolder,1,2.5k,,,Digikey,, $-   ,,
35,R46,R_0603_1608Metric_Pad1.05x0.95mm_HandSolder,1,1M,,,Digikey,, $-   ,,
36,"R47,R49",R_0603_1608Metric_Pad1.05x0.95mm_HandSolder,2,100k,,,Digikey,, $-   ,,
37,R51,R_0603_1608Metric_Pad1.05x0.95mm_HandSolder,1,820,,,Digikey,, $-   ,,
38,SW1,MOLEX_SL_04_Vertical,1,Relay_SPST-MRDT_Switches, ,,Digikey,, $-   ,,
39,U10,OKI_Horizontal,1,3V3 OKI,"DC DC CONVERTER 5V 8W	","811-2692-ND	",Digikey, $4.54 , $4.54 ,https://www.Digikey.com/product-detail/en/murata-power-solut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,
40,U12,OKI_Horizontal,1,5V OKI,DC DC CONVERTER 3.3V 5W,"811-3014-ND	",Digikey, $4.54 , $4.54 ,https://www.Digikey.com/product-detail/en/murata-power-solut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,
41,F1,Fuse_2920_7451Metric,1,Polyfuse,"PTC RESET FUSE 60V 750MA 2920	",507-1743-1-ND,Digikey, $0.28 , $0.28 ,https://www.digikey.com/product-detail/en/bel-fuse-inc/0ZCF0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,
42,"C10,C16",CP_Radial_D6.3mm_P2.50mm,2,22u 50V,CAP ALUM 22UF 20% 50V RADIAL,P837-ND,Digikey, $0.25 , $0.50 ,https://www.digikey.com/product-detail/en/panasonic-electron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,
43,C1,C_1206_3216Metric_Pad1.42x1.75mm_HandSolder,1,10u,CAP CER 10UF 50V X5R 1206,"490-12457-1-ND	",Digikey, $0.57 , $0.57 ,https://www.digikey.com/product-detail/en/murata-electronics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,
